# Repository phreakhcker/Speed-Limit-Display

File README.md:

# Speed Limit Display

A real-time speed limit display built with an ESP32, GPS module, and OLED screen. Shows the current road's speed limit with color-coded overspeed warnings (green/yellow/red).

Uses the TomTom Snap-to-Roads API for accurate road matching — sends your heading and speed so it picks the correct road, even near highway ramps and parallel roads.

## Hardware

| Component | Details |
|-----------|---------|
| Microcontroller | ESP32 Mini (any variant: original, S2, S3, C3) |
| GPS Module | Any NMEA-compatible (NEO-6M, NEO-7M, BN-220, etc.) |
| Display | SSD1351 128x128 SPI OLED |
| Button | One momentary pushbutton |
| Power | USB or 5V supply |

## Wiring

| ESP32 Pin | Connects To |
|-----------|-------------|
| GPIO 20 | GPS TX |
| GPIO 21 | GPS RX |
| GPIO 7 | OLED CS |
| GPIO 2 | OLED DC |
| GPIO 3 | OLED RST |
| GPIO 4 | OLED MOSI (SDA) |
| GPIO 6 | OLED SCLK (SCL) |
| GPIO 10 | Button (other leg to GND) |

Pin assignments can be changed in `config.h`.

## Features

- **Snap-to-Roads API** — sends GPS heading + speed for accurate road matching
- **GPS point buffering** — 5-point trajectory for better map matching
- **Speed limit smoothing** — rejects false readings from nearby roads
- **Overspeed alerts** — green (ok), yellow (close to limit), red (over limit) with hysteresis
- **Dual-core HTTP** — API calls on Core 0, GPS/display on Core 1 (no display freezes)
- **Non-blocking WiFi** — GPS keeps working during WiFi reconnects
- **API rate limiting** — exponential backoff on HTTP 429, daily quota tracking
- **Watchdog timer** — auto-reboots if the device freezes
- **One-button menu** — adjust brightness, alert thresholds, API timing, GPS reset
- **Persistent settings** — brightness and thresholds saved across reboots

## Setup

### 1. Install Arduino Libraries

Open Arduino IDE, go to **Sketch > Include Library > Manage Libraries** and install:

- **TinyGPSPlus** (by Mikal Hart)
- **ArduinoJson** (by Benoit Blanchon, version 6.x)
- **Adafruit GFX Library**
- **Adafruit SSD1351 Library**

### 2. Get a TomTom API Key (free)

1. Go to [developer.tomtom.com](https://developer.tomtom.com)
2. Create a free account
3. Go to Dashboard > My Apps > Add New App
4. Copy your API key (free tier = 2,500 requests/day)

### 3. Configure Credentials

1. In the `SpeedLimitDisplay/` folder, copy `config_secrets_example.h` to `config_secrets.h`
2. Edit `config_secrets.h` with your WiFi name, password, and TomTom API key
3. `config_secrets.h` is in `.gitignore` — it will never be uploaded to GitHub

### 4. Upload to ESP32

1. Open `SpeedLimitDisplay/SpeedLimitDisplay.ino` in Arduino IDE
2. Select your ESP32 board in **Tools > Board**
3. Click **Upload**

### 5. Serial Monitor (optional, for debugging)

Open **Tools > Serial Monitor** at 115200 baud. Type:
- **`d`** — full debug status dump
- **`r`** — reboot the device

## Button Controls

| Action | Normal Mode | Menu Mode |
|--------|------------|-----------|
| Short press | Cycle brightness | Next menu item |
| Long press (1.2s) | Enter menu | Change selected setting |
| Very long press (2.5s) | — | Exit menu |

## Configuration

All tunable settings (pins, timing, thresholds) are in `config.h`. Secrets (WiFi, API key) are in `config_secrets.h`.

## Custom PCB (v2)

A custom 2-layer PCB designed in KiCad 10.0 with everything on one board:

| Component | Details |
|-----------|---------|
| U1 | ESP32-S3-WROOM-1-N8 (dual core, 8MB flash, WiFi+BLE) |
| U2 | Quectel L70-R GPS module with ceramic patch antenna |
| U3 | LV75530PDBV 3.3V LDO regulator |
| J1 | USB-C connector (power + programming) |
| J2 | 12-pin display header |
| J4 | 9-pin breakout header (spare GPIOs + power for future expansion) |
| SW1 | EC11 rotary encoder with push button (menu navigation) |
| SW3/SW4 | Boot and reset buttons |
| BZ1 | Piezo buzzer (optional) |

Gerber files are in `PCB Design/.../Gerber/` ready to upload to PCBWay or JLCPCB.

See [docs/hardware/PCB_DESIGN.md](docs/hardware/PCB_DESIGN.md) for full design details, ordering instructions, and assembly guide.

## Project Structure

```
Speed-Limit-Display/
├── SpeedLimitDisplay/              # Arduino sketch folder
│   ├── SpeedLimitDisplay.ino       # Main code
│   ├── config.h                    # All tunable settings
│   ├── config_secrets.h            # Your credentials (git-ignored)
│   └── config_secrets_example.h    # Template for credentials
├── PCB Design/                     # KiCad PCB project
│   └── .../Speed-Limit-Display-v2/
│       ├── *.kicad_sch             # Schematic
│       ├── *.kicad_pcb             # PCB layout
│       ├── *.kicad_dru             # Custom DRC rules
│       └── Gerber/                 # Manufacturing files (.zip)
├── docs/
│   ├── hardware/
│   │   ├── PCB_DESIGN.md           # PCB specs, ordering, assembly guide
│   │   └── DRC_FIXES_CHECKLIST.md  # DRC fixes applied
│   └── PRODUCT_PLAN.md             # Product roadmap
├── .gitignore
├── CONTRIBUTING.md                 # How to contribute
├── LICENSE
└── README.md                       # This file
```

## Contributing

See [CONTRIBUTING.md](CONTRIBUTING.md) for how to set up your environment, create branches, and submit changes.

## License

See [LICENSE](LICENSE) for details.

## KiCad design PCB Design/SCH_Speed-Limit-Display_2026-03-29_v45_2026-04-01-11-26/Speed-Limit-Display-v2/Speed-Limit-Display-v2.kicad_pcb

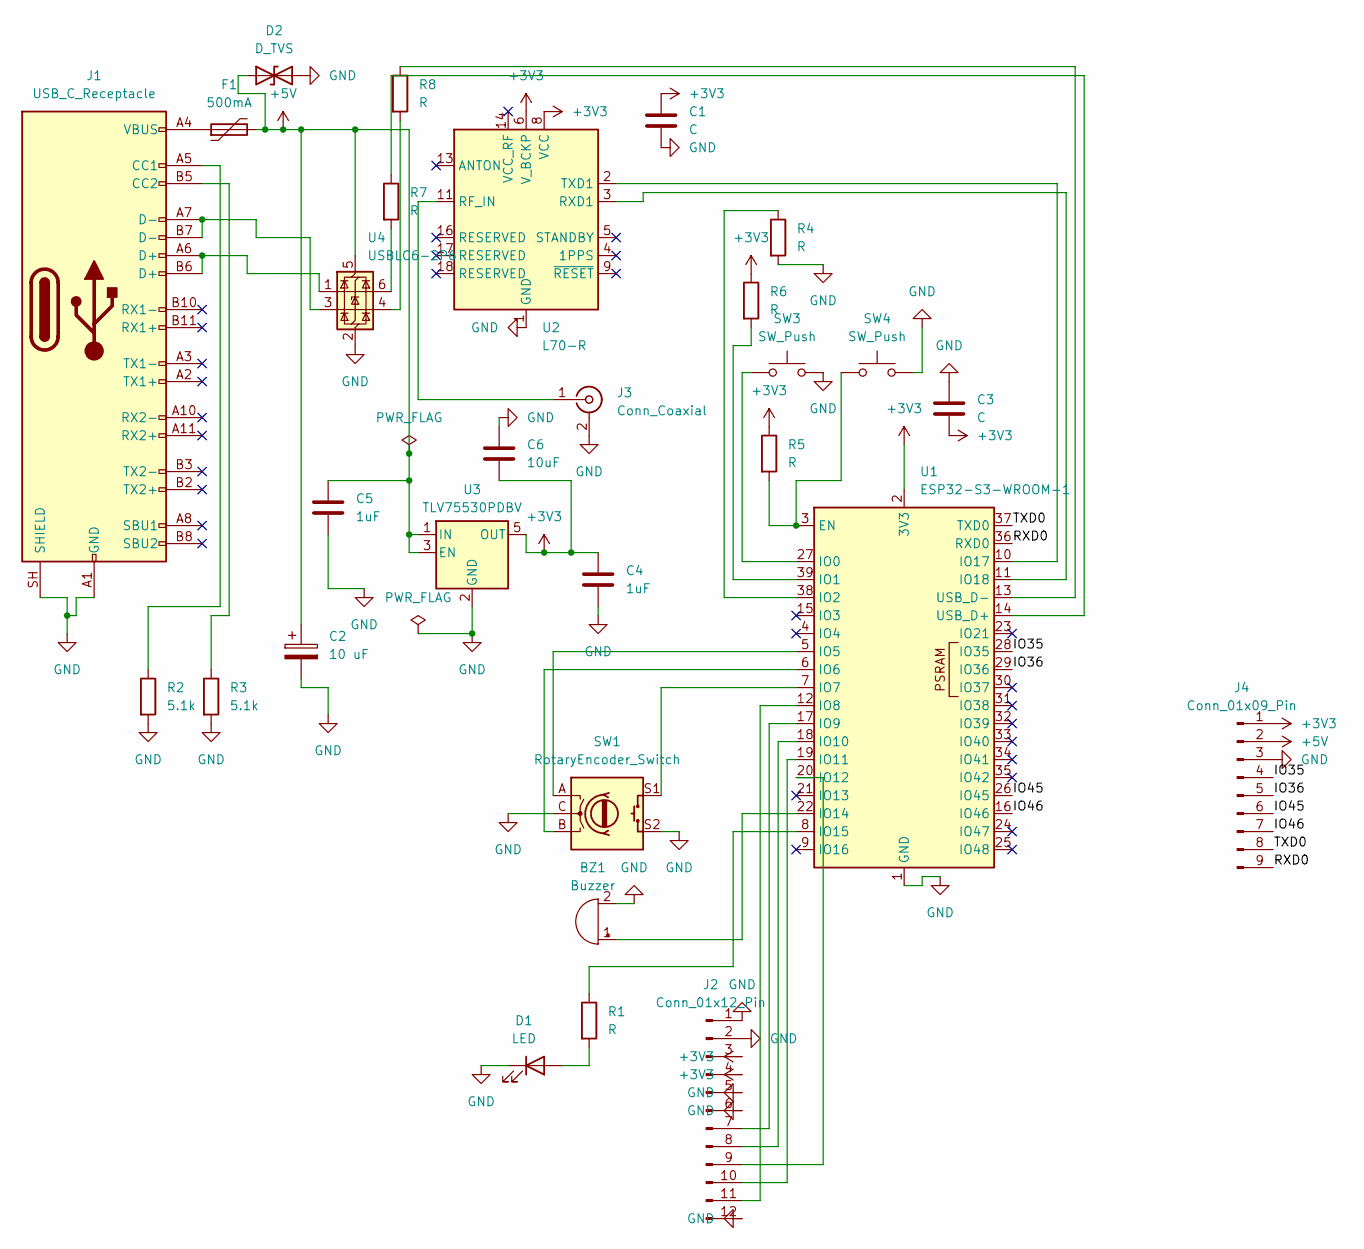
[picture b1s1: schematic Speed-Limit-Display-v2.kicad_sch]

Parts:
BZ1: Buzzer
C1, C3: C
C2: 10 uF
C4, C5: 1uF
C6: 10uF
D1: LED
D2: D_TVS
F1: 500mA
J1: USB_C_Receptacle
J2: Conn_01x12_Pin
J3: Conn_Coaxial
J4: Conn_01x09_Pin; PinHeader_1x09_P2.54mm_Vertical
R1, R4, R5, R6, R7, R8: R
R2, R3: 5.1k
SW1: RotaryEncoder_Switch
SW3, SW4: SW_Push
U1: ESP32-S3-WROOM-1
U2: L70-R; Quectel_L70-R
U3: TLV75530PDBV; SOT-23-5
U4: USBLC6-2P6; SOT-666

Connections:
+3V3: C1.1, C3.2, C4.1, C6.2, J2.3, J2.4, J4.1, R5.1, R6.1, U1.2 (3V3), U2.6 (V_BCKP), U2.8 (VCC), U3.5 (OUT)
+5V: C2.1, C5.1, D2.1 (A1), F1.2, J4.2, U3.1 (IN), U3.3 (EN), U4.5 (VBUS)
/IO35: J4.4, U1.28 (IO35)
/IO36: J4.5, U1.29 (IO36)
/IO45: J4.6, U1.26 (IO45)
/IO46: J4.7, U1.16 (IO46)
/RXD0: J4.9, U1.36 (RXD0)
/TXD0: J4.8, U1.37 (TXD0)
GND: BZ1.2 (-), C1.2, C2.2, C3.1, C4.2, C5.2, C6.1, D1.1 (K), D2.2 (A2), J1.A1 (GND), J1.A12 (GND), J1.B1 (GND), J1.B12 (GND), J1.SH (SHIELD), J2.1, J2.2, J2.5, J2.6, J2.12, J3.2 (Ext), J4.3, R2.2, R3.2, R4.2, SW1.C, SW1.S2, SW3.2, SW4.2, U1.1 (GND), U1.40 (GND), U1.41 (GND), U2.1 (GND), U2.10 (GND), U2.12 (GND), U3.2 (GND), U4.2 (GND)
unnamed: BZ1.1 (+), U1.22 (IO14)
unnamed: D1.2 (A), R1.2
unnamed: F1.1, J1.A4 (VBUS), J1.A9 (VBUS), J1.B4 (VBUS), J1.B9 (VBUS)
unnamed: J1.A5 (CC1), R2.1
unnamed: J1.B5 (CC2), R3.1
unnamed: J1.A6 (D+), J1.B6 (D+), U4.1 (I/O1)
unnamed: J1.A7 (D-), J1.B7 (D-), U4.3 (I/O2)
unnamed: J2.7, U1.17 (IO9)
unnamed: J2.8, U1.18 (IO10)
unnamed: J2.9, U1.20 (IO12)
unnamed: J2.10, U1.19 (IO11)
unnamed: J2.11, U1.12 (IO8)
unnamed: J3.1 (In), U2.11 (RF_IN)
unnamed: R7.2, U4.6 (I/O1)
unnamed: R8.2, U4.4 (I/O2)
unnamed: R5.2, SW4.1, U1.3 (EN)
unnamed: SW3.1, U1.27 (IO0)
unnamed: R6.2, U1.39 (IO1)
unnamed: R4.1, U1.38 (IO2)
unnamed: SW1.A, U1.5 (IO5)
unnamed: SW1.B, U1.6 (IO6)
unnamed: SW1.S1, U1.7 (IO7)
unnamed: R1.1, U1.8 (IO15)
unnamed: U1.10 (IO17), U2.2 (TXD1)
unnamed: U1.11 (IO18), U2.3 (RXD1)
unnamed: R7.1, U1.14 (USB_D+)
unnamed: R8.1, U1.13 (USB_D-)

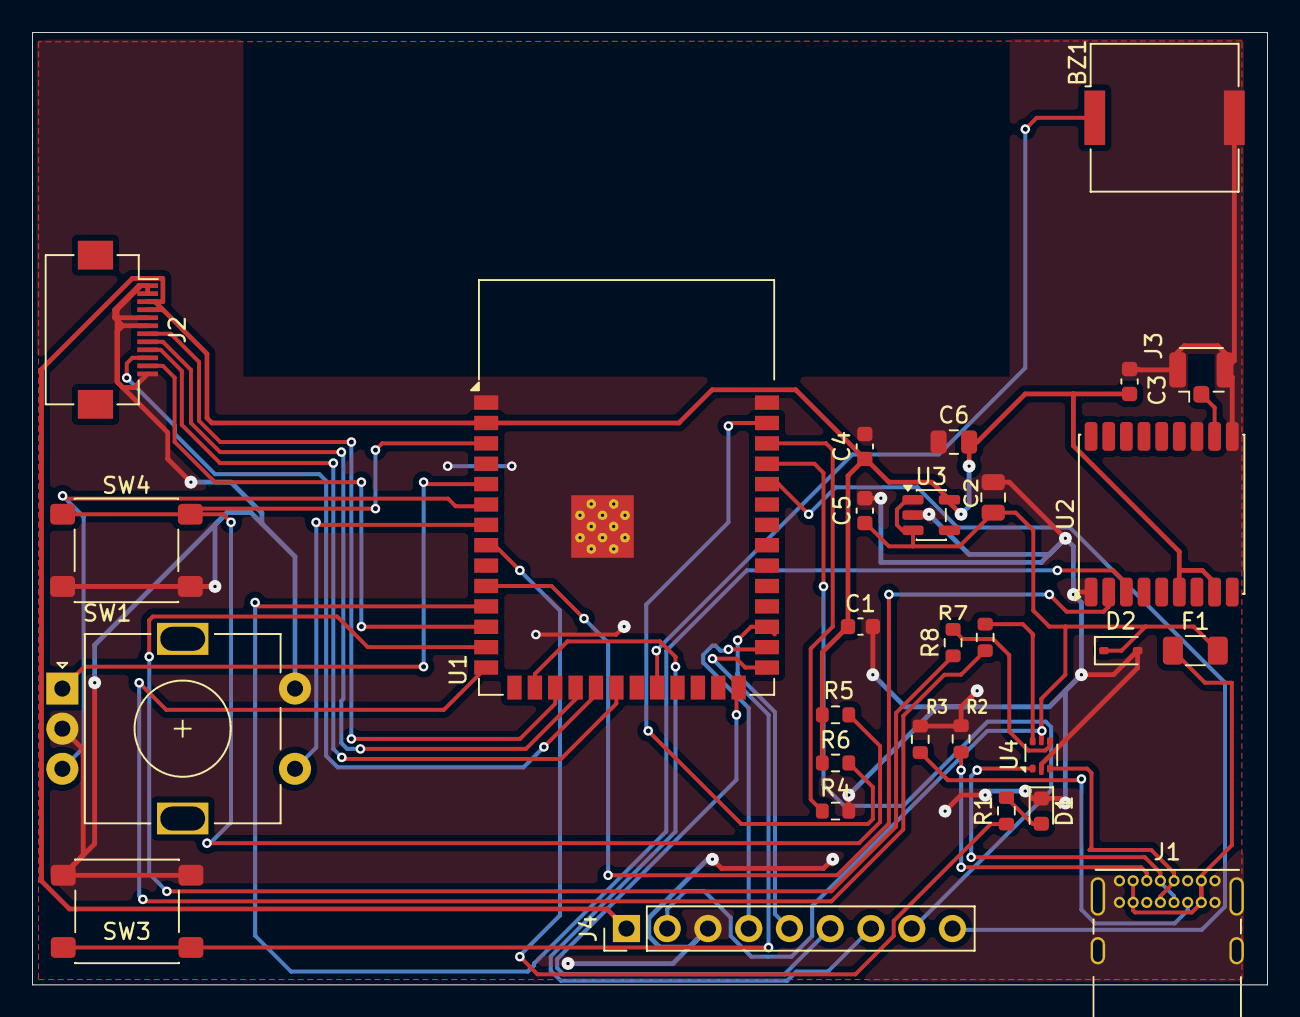
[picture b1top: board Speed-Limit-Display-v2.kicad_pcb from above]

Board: 2 copper layers, 77.0 x 59.4 mm, 29 parts (0 on the bottom side), 36 nets.
